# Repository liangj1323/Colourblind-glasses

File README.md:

# Colourblind-glasses
My file for colourblindness glasses:

I will make the onshape and the PCB design here.

Onshape when exporting parts I don't know if they worked properly, so there is the main one, but 3 extra ones which are the three parts that the main one are made out of in case the main one is actually only one of them

I also multi uploaded the Kicad files in case it didn't work!

Here is a detailed explanation of the essay this idea is based on the competition me and my team used this for!

A quick introduction
Colour vision deficiency (CVD or more commonly referred to as colour blindness) affects approximately 8% of men and 0.5% of women worldwide, which totals 300 million people in total - more than 4 times the population of the UK. The most common form of this is called red-green CVD, where the person finds it hard to tell between brown and orange shades.

How we come in 
Our concept is simple, yet original – active OLED-based glasses that use real-time image processing to help colour separation for most types of CVD. Instead of using colour filters like other brands, these glasses trick your disability into the opposite way!
Our idea helps people with CVD but can also help other communities. This problem is currently a large but unseen problem in our society. There are so many people in the world with this disability: nearly 10%! When our idea works, colourblind people’s lives will get better, and they can see the world correctly – this disease makes all sorts of simple tasks from reading colour-coded maps, to identifying ripe fruit more difficult.

Looking into CVD in detail
CVD is a genetic condition: this means that this condition is inherited from family although it can be a cause of other diseases, ageing, drugs or medication. To understand how CVD ‘works’ we can look at how the normal eye works.
When light enters the eye, it triggers loads of photoreceptor cone cells that detects different colours. Normal colour vision is when your cones are used to the right wavelength (e.g. red is 560nanometers). The three cones (RGB) are sensitive to their colours so when you see a certain colour, it triggers the ratio of activation relative to all the cones and will send that signal to your brain - since we are adapted to this, we can see more than 6,000,000 different colours.
Most CVD occurs when there is an overlapping sensitivity between the cones, causing your brain to muddle up the different hues which become indistinguishable. E.g. for red-green CVD, this is caused by the overlapping sensitivity between the red (L-cone) and green photoreceptors (M-cone).

How do we fix this?
Filtered glasses are often inaccurate and unreliable, but we fix this problem. On both sides are cameras that will transmit information to a mainboard (Raspberry Pi-0-2W mainboard) which has 512MB of memory, Bluetooth, and several ports to connect to cameras, etc. We can implement one in our glasses’ frame or place them in a pocket nearby.
The processor runs a real-time colour correction algorithm designed specifically and transmits the information onto the OLED lenses. This display will create an overlay aligned with the real world. Here is our process in a nutshell.
Firstly, the cameras continuously record the user’s surroundings. The camera is aligned with the user’s sight and peripheral vision, so the image later shown can align with reality. The mainboard applies our colour correction algorithm which consists of it simulating how a colourblind viewer perceives the scenes using Brettel or Machado. Then it modifies the image to singular pixels of hex colours to increase the distance between colours which then is outputted as a different colour. At this step, other factors can be inputted like the brightness of the outside world to be factored to make the output better. For example, for red-green CVD, reds are shifted slightly towards magenta, and the saturation can be increased.
The corrected image is then combined using the hex values and unchanged pixels are deleted, this information is transmitted and then displayed on transparent OLED lenses. OLED lenses work best since they produce high contrast, so they are ideal for overlaying enhanced colour information without blocking the user’s natural view.
Why us? 
Using OLED-based glasses to fix disabilities is a completely empty market. The only ‘famous’ use of colour-blindness glasses is EnChroma, but they only help 4/5 of people and use passive filters that remove specific wavelengths of light. As well as only helping some, it can also be unreliable and cannot dynamically adapt to different environments. 
Our product will be cheaper than EnChroma’s (see below). We solve all the problems with the other companies using similar technology. E.g. take the Apple Vision which uses transparent OLED technology. Their technology is bulky and uncomfortable to wear – ours are lightweight: all parts of the glasses are discreet and made to be extremely similar to normal glasses (see diagram 1).
All the data of our glasses is also locally handled, unlike Ray-Ban’s glasses. Executing this idea might not be easy - we would have to offer some insurance policy. There are no big companies which are in the position who could copy this, as this would not fit their style. No part of this clash with any existing copyrights/patents, since EnChroma only has patents on filters. 
Our profit would be about £35.05 per pair or a 30% profit margin
 
We are cheaper than competitors like EnChroma, at least £50 cheaper or even 2 times!
Further research
Firstly, we want to explore a simpler extension to the glasses. On the Raspberry Pi module we are using, there is already Bluetooth. We can make the Bluetooth connect to an app. This means that users can control their details of how to customize the glasses’ functions to their needs. 
Excluding CVD, there are other big diseases that we could also be helped with our glasses. These include visual agnosia, ADHD, dyslexia and CDS. The main idea is that if we swap out our camera for a Raspberry Pi AI camera or embed a LLM into the mainboard, our glasses have the capabilities to name objects. It could reconfigure how sure it is on each object and help with these diseases by visually labelling.
This would work best for visual agnosia, which is when your brain can’t link what you see a certain word, and needs that ‘push’ to remember. We could make a label to remind you so you can instantly know what said object is.
This also helps with other diseases as well: ADHD can be helped by training your attention with cues and colour-coded systems; dyslexia could be helped with labels in the form of emojis or pictures; and CDS can be helped by labelling things in a cluttered environment to lower the cognitive load of the brain. All these ways to help other disabilities are based on one core idea, which would link to our Bluetooth idea.
Our final idea is more ambitious. Since we have so many different usages, what if instead of different glasses, we used different lenses? The idea is that each lens would connect to the main frame using some magnet slide. It would then transmit to the mainboard its use and the mainboard could switch to be different functions (see below). This means we could sell our frame for £85 and sell the lenses separately. This would boost our sales while keeping our cheap price. We can then run more promotional events (e.g. buy 4 lenses get 1 free). This would boost our sales, meaning we could sell more to earn more profit since our profit margin isn’t that big.

Sources:
https://docs.google.com/document/d/1gaUPH-cYD800do3NKkF9AClcoWa02SfzEE7OkMBLKK0/edit?usp=sharing

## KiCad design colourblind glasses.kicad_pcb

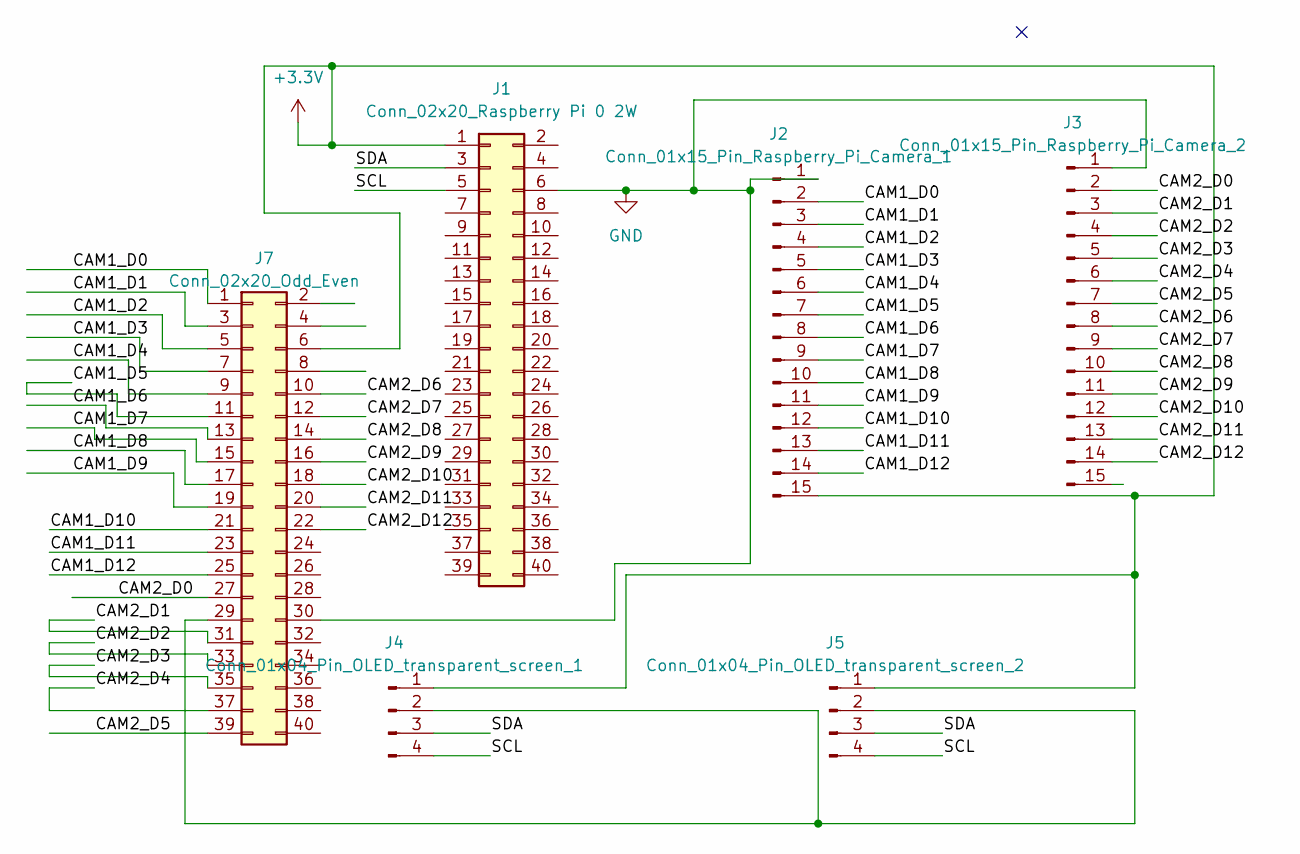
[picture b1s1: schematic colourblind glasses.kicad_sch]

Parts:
J1: Conn_02x20_Raspberry Pi 0 2W; PinSocket_2x20_P2.54mm_Vertical
J2: Conn_01x15_Pin_Raspberry_Pi_Camera_1; Hirose_FH12-15S-0.5SH_1x15-1MP_P0.50mm_Horizontal
J3: Conn_01x15_Pin_Raspberry_Pi_Camera_2; Hirose_FH12-15S-0.5SH_1x15-1MP_P0.50mm_Horizontal
J4: Conn_01x04_Pin_OLED_transparent_screen_1; PinHeader_1x04_P2.54mm_Vertical
J5: Conn_01x04_Pin_OLED_transparent_screen_2; PinHeader_1x04_P2.54mm_Vertical
J7: Conn_02x20_Odd_Even; PinHeader_2x20_P2.54mm_Vertical

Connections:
+3.3V: J1.1, J2.15, J4.1, J5.1, J7.6
/CAM1_D0: J2.2, J7.1
/CAM1_D1: J2.3, J7.3
/CAM1_D2: J2.4, J7.5
/CAM1_D3: J2.5, J7.7
/CAM1_D4: J2.6, J7.9
/CAM1_D5: J2.7, J7.11
/CAM1_D6: J2.8, J7.13
/CAM1_D7: J2.9, J7.15
/CAM1_D8: J2.10, J7.17
/CAM1_D9: J2.11, J7.19
/CAM1_D10: J2.12, J7.21
/CAM1_D11: J2.13, J7.23
/CAM1_D12: J2.14, J7.25
/CAM2_D0: J3.2, J7.27
/CAM2_D1: J3.3, J7.31
/CAM2_D2: J3.4, J7.33
/CAM2_D3: J3.5, J7.35
/CAM2_D4: J3.6, J7.37
/CAM2_D5: J3.7, J7.39
/CAM2_D6: J3.8, J7.10
/CAM2_D7: J3.9, J7.12
/CAM2_D8: J3.10, J7.14
/CAM2_D9: J3.11, J7.16
/CAM2_D10: J3.12, J7.18
/CAM2_D11: J3.13, J7.20
/CAM2_D12: J3.14, J7.22
/SCL: J1.5, J4.4, J5.4
/SDA: J1.3, J4.3, J5.3
GND: J1.6, J2.1, J3.1, J7.30
unnamed: J4.2, J5.2, J7.29

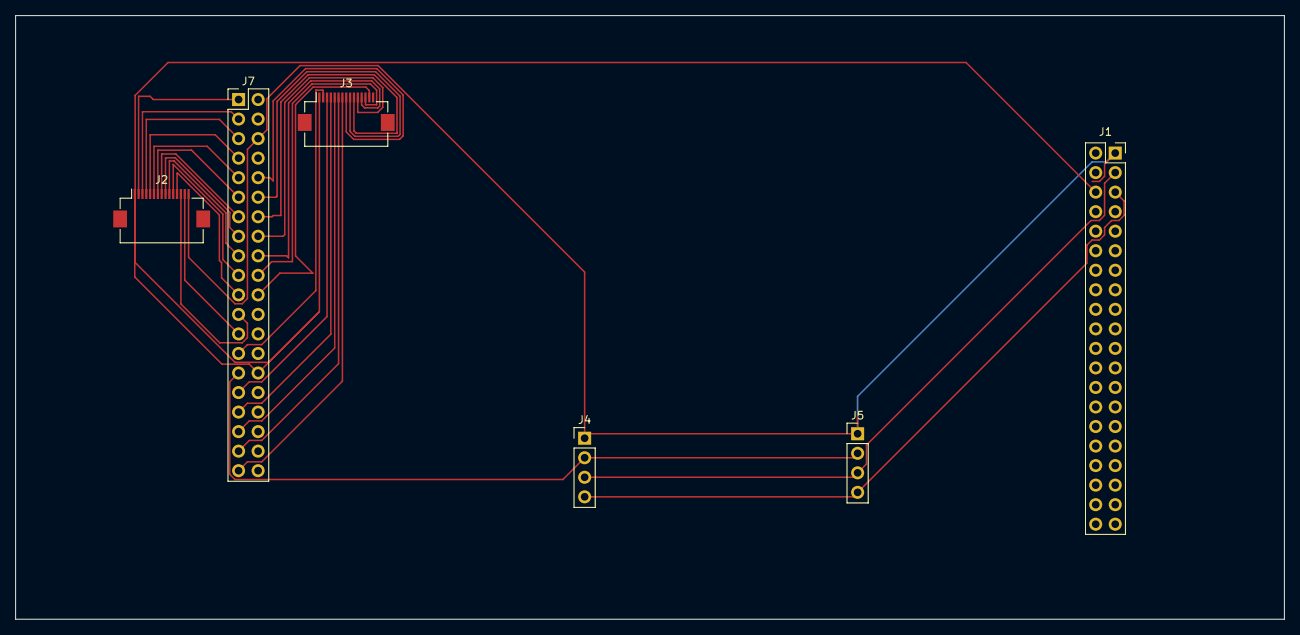
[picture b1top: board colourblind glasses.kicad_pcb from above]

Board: 2 copper layers, 165.0 x 78.5 mm, 6 parts (0 on the bottom side), 31 nets.
